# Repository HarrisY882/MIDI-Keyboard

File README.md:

# MIDI-Keyboard
this is a project, similar to a pinao in which i designed, using kai pereiras help, with his guide. However i dsigned the schematic and pcb m=by myself, This was a great learning experience, espceially teaching me how to deal with and use different pcb layers.
I spend around 7 hours on this project which was quite along time, and i had many errors, for example, with footprints, they were not synced therefore leading me confused why the xiao footprints werent linked with the touch sensors.
Altogether, this is my final Pcb and schematic design:

And here is a 3d model of the pcb:

Altogether im pleased with the design and how ive done it. My favoutite part of this project was designing the footprints, and learning about b.cu

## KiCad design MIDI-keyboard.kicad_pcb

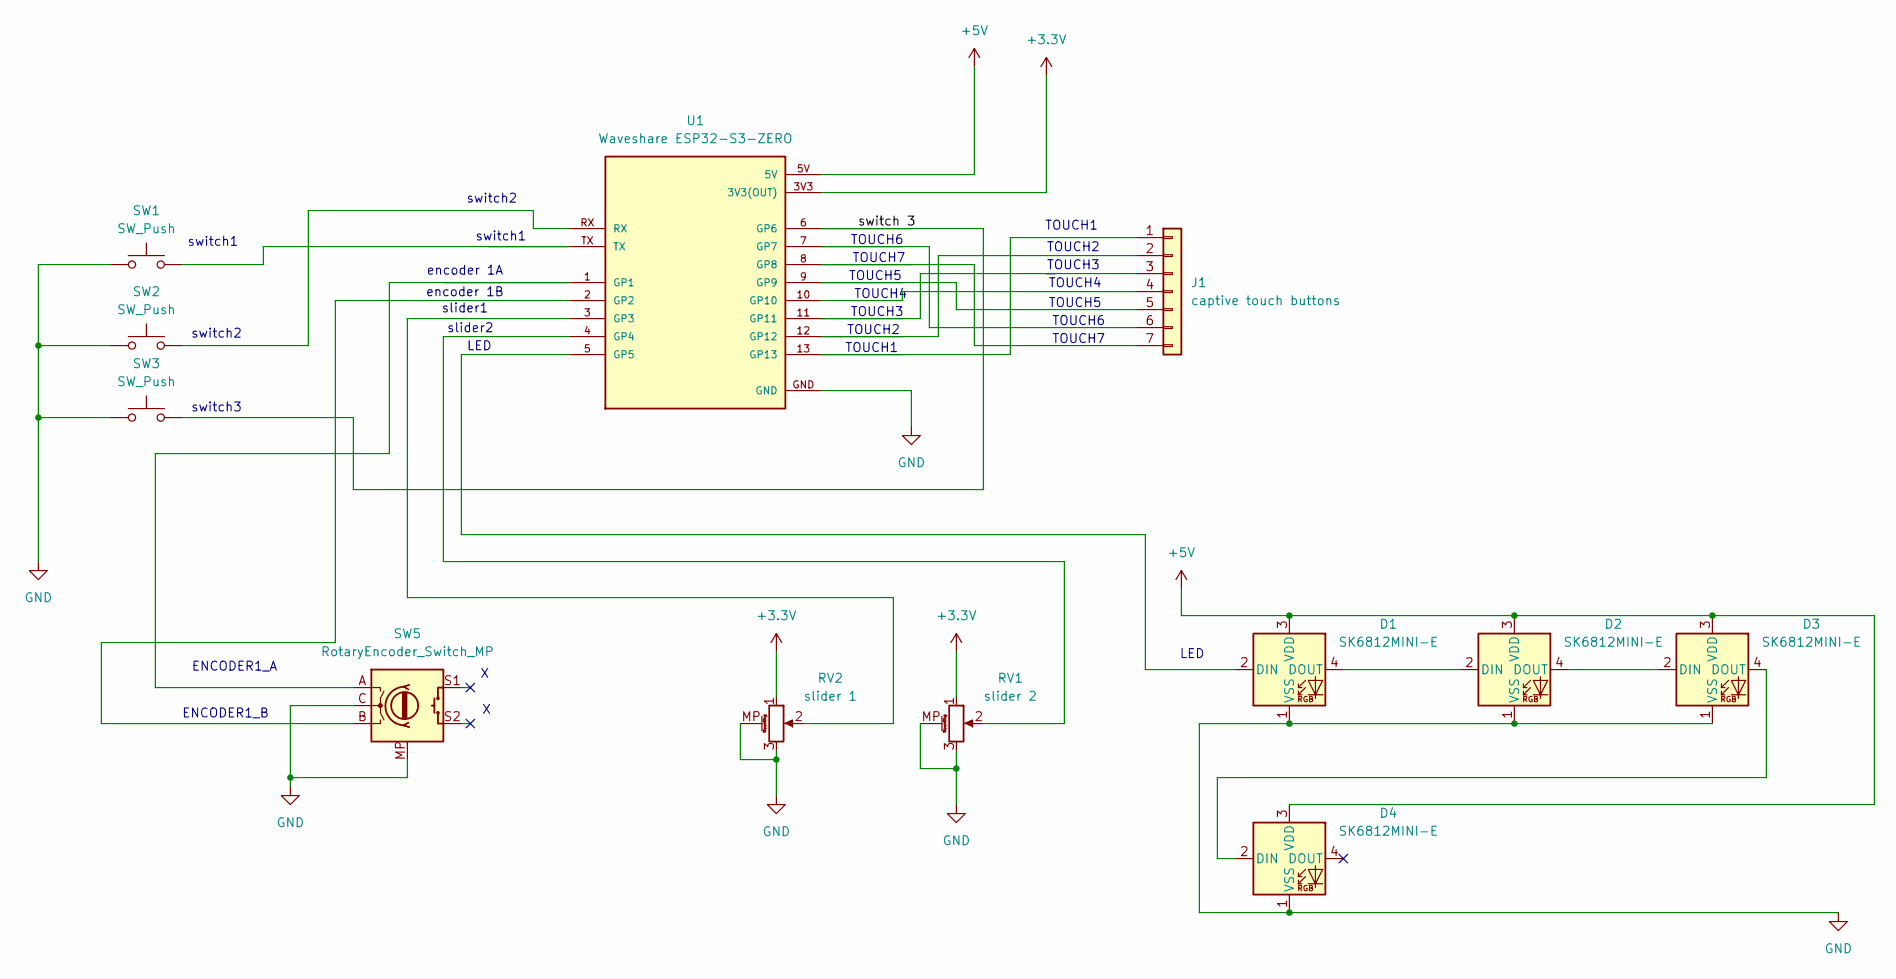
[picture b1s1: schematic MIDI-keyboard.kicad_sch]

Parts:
D1, D2, D3, D4: SK6812MINI-E; LED_SK6812MINI-E_3.2x2.8mm_P1.5mm_ReverseMount
J1: captive touch buttons; pianofootprint
RV1: slider 2; Potentiometer_Bourns_PTA1543_Single_Slide
RV2: slider 1; Potentiometer_Bourns_PTA1543_Single_Slide
SW1, SW2, SW3: SW_Push; Kailh Choc Low-Profile Switches
SW5: RotaryEncoder_Switch_MP; RotaryEncoder_Alps_EC11E-Switch_Vertical_H20mm
U1: Waveshare ESP32-S3-ZERO; Waveshare ESP32-S3-Zero; PARTREV NA

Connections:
+3.3V: RV1.1, RV2.1, U1.3V3 (3V3(OUT))
+5V: D1.3 (VDD), D2.3 (VDD), D3.3 (VDD), D4.3 (VDD), U1.5V
/switch 3: SW3.2, U1.6 (GP6)
GND: D1.1 (VSS), D2.1 (VSS), D3.1 (VSS), D4.1 (VSS), RV1.3, RV1.MP (MountPin), RV2.3, RV2.MP (MountPin), SW1.1, SW2.1, SW3.1, SW5.C, SW5.MP, U1.GND
unnamed: D1.2 (DIN), U1.5 (GP5)
unnamed: D1.4 (DOUT), D2.2 (DIN)
unnamed: D2.4 (DOUT), D3.2 (DIN)
unnamed: D3.4 (DOUT), D4.2 (DIN)
unnamed: J1.1, U1.13 (GP13)
unnamed: J1.2, U1.12 (GP12)
unnamed: J1.3, U1.11 (GP11)
unnamed: J1.4, U1.10 (GP10)
unnamed: J1.5, U1.9 (GP9)
unnamed: J1.6, U1.7 (GP7)
unnamed: J1.7, U1.8 (GP8)
unnamed: SW1.2, U1.TX
unnamed: SW2.2, U1.RX
unnamed: SW5.A, U1.1 (GP1)
unnamed: SW5.B, U1.2 (GP2)
unnamed: RV2.2, U1.3 (GP3)
unnamed: RV1.2, U1.4 (GP4)

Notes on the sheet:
TOUCH2
TOUCH6
encoder 1B
slider2
TOUCH4
TOUCH7
TOUCH5
TOUCH1
ENCODER1_B
TOUCH3
switch2
LED
encoder 1A
ENCODER1_A
switch1
switch2
slider1
switch3
LED

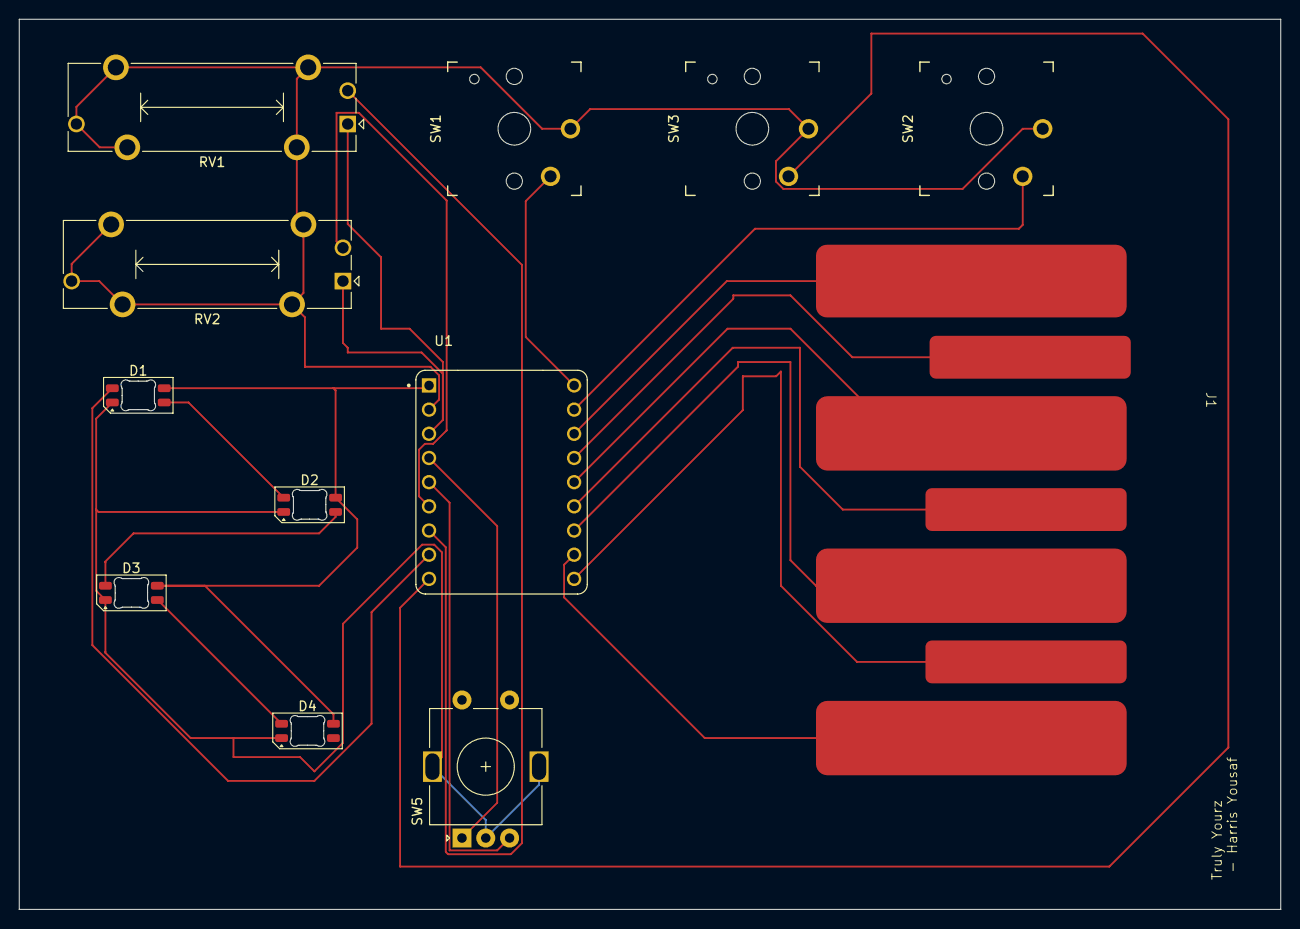
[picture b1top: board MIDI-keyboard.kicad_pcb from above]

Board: 2 copper layers, 132.5 x 93.5 mm, 12 parts (0 on the bottom side), 21 nets.
